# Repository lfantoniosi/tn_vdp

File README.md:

# TN VDP 

# Latest updates:

## 2023-06-20: V3 Main Board with audio fix (Tang20k only)

New V3 board with audio fix has been submitted. Check the kicad folder for gerbers. It requires few new components that you can read on the board. Pretty simple: 10uf capacitor and an optional cinch connector. I will not be updating the BOM lists. WIP project. For a 9958 socket, turn off GromClk (Jumper 3). Leave CpuClk on (Jumper4).

## 2023-06-20: V9958 Socket (V3 Tang20K)

The V9958 drop-in socket (SDIP-64) has been submitted. Check the kicad folder. Code has been improved for Omega MSX compatibility. SDIP pin header are hard to find. Check AliExpress for **"1.778mm Pitch Single Row Male Round Pin Header"**. Not including links they aren't persistent. You need a V3 main board as well for the Tang20K. 

**Note** My Omega MSX has the RAM expansion module and I found out it has incompatiblity with the Tang (seems to be too noisy). If you get issues with IDE controllers, try removing some RAM chips from higher banks. I left my Omega with only 2MB. It's not a PSU problem but rather a routing issue that plagues the Omega for some time.

# Project details
 
## Tang Nano 9K TMS9118A VDP

This project recreates the TMS9118A (and its TMS9928A/TMS9929A
variants) in FPGA using the over the counter Sipeed's Tang Nano 9K
board plus a designed set of boards to be stacked on top where the
TMS9118 was located.

TN VDP v1 uses
[Matthew Haggerty's F18A core](https://github.com/dnotq/f18a), which
is completely compatible with the original Texas Instruments VDP, but
adds
[additional video modes, sprites and color capabilities](https://dnotq.io/f18a/intro.html).

The bitstream file is [here](fpga/tn_vdp_v1/impl/pnr/tn_vdp.fs)

## Version 2.0

The new version supports audio over HDMI. There is no more VGA output. You'll need to pull the pre-amplified audio from somewhere in the computer and connect the **AUDIO** pin on the tn-vdp socket. **MODE1** is not used for TMS9918 cores.

This requires the v2 board sets as well the v2 bitstream (socket board + mainboard). See below gerber files.

There are 2 bitstreams for v2:

[TMS9918](fpga/tn_vdp_v2_v9918/impl/pnr/tn_vdp.fs)

## V9958 32KB VRAM

There is a new core for the v2 boards implemented from ESE-MSX3. The bitstream can be used on the same v2 board sets for the TMS9918:

[V9958](fpga/tn_vdp_v2_v9958/impl/pnr/tn_vdp_v9958.fs)

But for the V9958 you need to pull the A1 address line from somewhere in the computer and connect to pin **MODE1** on the socket to use the full capabilites of the V9958.

## V9958 128KB VRAM: Tang Nano 20K

The v3 of the fpga code and mainboard is for use on a Tang Nano 20K only. There are no other versions for Tang Nano 20K other than V9958 128K. If you need a 9918 use the Tang Nano 9K instead. The socket for the TMS9118 is the same from v2. A socket for a V9958 replacement is in the works.

See instructions below for programming it.

**Note** The gromclk signal has been retired from V9958 128K (no MSX ever uses it). So instead turning this jumper on puts the VDP in no-wait mode, full speed 27Mhz. Turning off it makes the VDP at normal speed (for VDP commands).

## NABU PC Floppy images

Bootable 80 colums for NABU PC CP/M 3 images can be downloaded here (flux and HxC2001): 

[NABU PC images](https://drive.google.com/file/d/1nU48-01ozhA_n-ZHN1SCNINqFqhcBxUN/view?usp=sharing)

## Gerber files

The gerber files can be located inside each KiCad project:

### V1 Boards
[MainBoard for NABU](kicad/tn_vdp_v1_slim/gerber.zip)

[MainBoard for TI-99/4A (FAT)](kicad/tn_vdp_v1_fat/gerber.zip)

[VGA breakout](kicad/tn_vdp_v1_vga/gerber)

[Compact board using SMD components](kicad/tn9k_f18a_compact/gerber.zip)
See the [separate README](kicad/tn9k_f18a_compact/README.md) for BOM ipand additional information.

The VGA module is optional, only if you want VGA output.

### V2 Boards

[MainBoard v2](kicad/tn_vdp_v2_board/gerber.zip)

[Socket v2](kicad/tn_vdp_v2_socket/gerber.zip)

### V3 Boards: Tang Nano 20K ONLY!

[MainBoard v3](kicad/tn_vdp_v3_board/gerber.zip)

[Socket v2](kicad/tn_vdp_v2_socket/gerber.zip) (same TMS9918 socket as v2)

## Gowin IDE
Follow this link to install the Gowin's IDE:

**Note: The code can be built and programmed using the latest Education Version 1.9.8.11 - The Education EDA does not require a license. DO NOT USE THE BETA EDA/PROGRAMMER.**

[IDE Installation](https://wiki.sipeed.com/hardware/en/tang/Tang-Nano-Doc/install-the-ide.html)

The FPGA series is GW1NR and the Device is GW1NR-9C. Use Embedded Flash Mode for permanent programming. Make sure the bitstream is set to Load Rate of 25Mhz (or higher) in the Project -> Configuration -> BitStream: Loading Rate (MHZ). The maximum for this device is 25 Mhz.

## Programming the FPGA

**Gowin Programmer**
Together Gowin IDE you find the programmer or you can install the programmer stand alone. Check the Gowin IDE instructions

**openFPGALoader**
Alternatively you can use the openFPGALoader but it requires changing the FTDI drivers through zadig. Follow the official page for instructions

The [openFPGALoader](https://github.com/trabucayre/openFPGALoader)
tool can be used to program the FPGA from the command line.

```
sudo openFPGALoader -b tangnano9k tn_vdp.fs
```

## Standalone test

The board has a standalone boot screen when you connect it to the USB-C and HDMI only. This will tell the FPGA has been programmed with success.

The v3 Tang Nano 20K has no standalone boot screen.

## Building:

The Tang Nano 9K board can be purchased on AliExpress or ebay.

The boards gerber files are inside each kicad project gerber folders.

## V1 BOM

The BOM for the NABU and FAT v1 variants can be found here [DigiKey BOM](https://www.digikey.ca/short/2t98zrjw)

Or transcribed here
```
Qty | Part Number                | Description
----+----------------------------+----------------------------------
1x  | 123-A-HDF15A-KG-TAXB-ND    | CONN D-SUB HD RCPT 15P R/A SLDR
3x  | 123-AR20-HZL-TT-ND         | CONN IC DIP SOCKET 20POS TIN
2x  | S7022-ND                   | CONN HDR 24POS 0.1 TIN PCB
1x  | 449-KT04RTH-ND             | SWITCH SLIDE DIP 4POS 25MA 24V
3x  | 296-8503-5-ND              | IC TXRX NON-INVERT 3.6V 20DIP
3x  | 1109PHCT-ND CAP            | CER 0.1UF 50V X7R AXIAL
2x  | 2057-PH2RA-16-UA-ND        | CONN HEADER R/A 16POS 2.54MM
2x  | A835AR-ND                  | CONN HDR DIP POST 20POS GOLD
1x  | ED3048-5-ND                | CONN IC DIP SOCKET 40POS TIN
1x  | 2057-ICM-640-1-GT-HT-ND    | MACHINE PIN SOCKET, IC, DIP, 40P
1x  | 1528-5294-ND               | GPIO RIBBON CABLE 2X10 IDC CABLE
3x  | CF14JT2K20CT-ND            | RES 2.2K OHM 5% 1/4W AXIAL
2x  | CF14JT47R0CT-ND            | RES 47 OHM 5% 1/4W AXIAL
3x  | CF14JT4K70CT-ND            | RES 4.7K OHM 5% 1/4W AXIAL
3x  | CF14JT1K00CT-ND            | RES 1K OHM 5% 1/4W AXIAL
3x  | F14JT470RCT-ND             | RES 470 OHM 5% 1/4W AXIAL
1x  | 497-4547-1-ND              | DIODE SCHOTTKY 20V 1A DO41
```
**Notes:**

1) CONN HDR DIP POST 20POS GOLD: It is expensive on DigiKey but it can be sourced elsewhere cheaper, even Amazon.
2) GPIO RIBBON CABLE 2X10 IDC CABLE : It was supposed to be 2x8 but is out of stock. The 2x10 just works. Or build your own.
3) The capacitors need to be soldered manually on the bottom of each IC's. There are no pads for them to reduce the size of the board. See back.jpg photo for reference under images folder.
4) There are 2 DIP 40 sockets in this list: one machined other normal. The machined socket you will use to connect the board on top, thus protecting the pins. The machined pins for the board will connect easily to a machined socket. Then you stack this machined socked over the normal one (notice little force is necessary), and then finally you stack them at the NABU PC's TMS9118 socket. This will protect both the NABU and the tn_vdp pins.

# V2 BOM
```
Qty | Part Number                | Description
----+----------------------------+----------------------------------
3x  | 123-AR20-HZL-TT-ND         | CONN IC DIP SOCKET 20POS TIN
1x  | 2057-ICM-308-1-GT-HT-ND    | MACHINE PIN SOCKET, IC, DIP, 8P
3x  | 296-8503-5-ND              | IC TXRX NON-INVERT 3.6V 20DIP
4x  | BC1084CT-ND                | CAP CER 0.1UF 50V X7R RADIAL
1x  | 1528-5294-ND               | GPIO RIBBON CABLE 2X10 IDC CABLE
1x  | 497-4547-1-ND              | DIODE SCHOTTKY 20V 1A DO41
1x  | MCP3202-CI/P-ND            | IC ADC 12BIT SAR 8DIP
2x  | S7022-ND                   | CONN HDR 24POS 0.1 TIN PCB
2x  | A835AR-ND                  | CONN HDR DIP POST 20POS GOLD
4x  | 732-5301-ND                | CONN HEADER VERT 20POS 2.54MM 
1x  | 10129379-920001BLF-ND      | CONN HEADER R/A 20POS 2.54MM
4x  | S9000-ND                   | CONN JUMPER SHORTING TIN
```
**Notes:**

I find these header pins 2.54mm too expensive on DigiKey. I'd advise you to procure them on AliExpress, longer wait time but way cheaper. 

# V3 BOM

The V3 BOM is almost identically to V2 except that I added a trimmer for the audio and I returned with the DIP switch 4 pos:

```
Qty | Part Number                | Description
----+----------------------------+----------------------------------
1x  | 3339P-1-103LF              | TRIMMER 10K OHM 0.5W PC PIN TOP
1x  | 449-KT04RTH-ND             | SWITCH SLIDE DIP 4POS 25MA 24V
```

## Jumper Settings

These are the jumper. Closed means ON:
```
USR1 : SPR MAX - Turn it on for 32 sprites per line (9958 this puts 8 sprites for mode 0)
USR2 : SCANLIN - Turn it on for scanlines
USR3 : GROMCLK - Turn it on to have GROM CLOCK enabled, Disabling it puts CPUCLK on pin 37 (9128/29)
USR4 : CPUCLK  - Turn if on to have CPU CLOCK on pin 38 (9929/29 and 9128/29)
```

## Assembling Instructions

You shouldn't have problem assembling it as all components are labeled. Just remember the 2 pin strips for the TMS9118 slot goes under the board as well the 3 caps. Everything else it on the top side. I personally prefer soldering the female header on the FPGA board. Mind the orientation of the **DIP switch** as the image below.
```
1) solder the 3 DIP-20 sockets on top side
2) for each socket, solder one axial caps under the board connecting pins GND and VCC the back image below
3) solder the mini-switch on top side, mind hte numbering according to the text
4) solder the two male machine strips under the board (20 pins each strip)
5) solder the male pins that came with the Tang Nano 9K board on the top side of the board (24 pins each)
6) solder the 8x2 right angle header (optional for VGA)
6) solder the 2 female headers under the Tang Nano 9K board
7) install the 3 74VLC256 chips. Mind the half-moon orientation
7) plug the Tang Nano 9K on the male pins, mind the HDMI and UBS-C orientation as printed on the board
8) configure the dip-switches
```

## DIP switches
```
USR1 - 32 sprite per line (TMS9918), 8 sprites per line (V9958)
USR2 - scanlines
USR3 - pin 37: gromclk (on), cpuclk (off)
USR4 - pin 38: cpuclk (on), NC (off)

TMS9918A: (NABU-PC, CX5M)
USR3 - on
USR4 - on

TMS9928/29A
USR3 - on
USR4 - off

TMS9918
USR3 - on
USR4 - on

TMS9128/29
USR3 - off
USR4 - off
```

## V3 Programming

The Tang Nano 20K version is a bit more convoluted to install. We need to reconfigure the PLL nets.

First using the programmer flash this LITEX on the board:

[Tang Nano 20K LITEX](fpga/tn_vdp_v3_v9958/res/pnr/tang_nano_20k_litex.fs)

Disconnect and re-connect to your PC.

Go to device manager and change the properties for the USB Serial Port (COMxx) for your Tang Nano 20K (disconnect/reconnect the board and see wich one disappear to identify it). Change the Port Settings: Bits per second to 115200 and Apply.

Now you need a terminal application like Tera Term to connect to serial port.

Pressione Control-X Control-C and ENTER

You should see the LITE terminal, type:

```
pll_clk O0=50M
pll_clk O1=125M
pll_clk -s
```

After that you can just flash the v3 core from here:

[V9958 128K](fpga/tn_vdp_v3_v9918/impl/pnr/tn_vdp_v3_v9958.fs)

Now the board is ready to use.

## Images

You need to solder the capacitors under each IC's. I made this way to reduce the size of the board.

And the final board stacked up. To avoid plugging the board inverted there are two labels on it: **USB-C SIDE** and **HDMI SIDE**. The orientation of the board towards the TMS9118 slot is the USB-C up (pin 1 of TMS9118). The TMS9118 pin number 1 and 40 are printed under it.

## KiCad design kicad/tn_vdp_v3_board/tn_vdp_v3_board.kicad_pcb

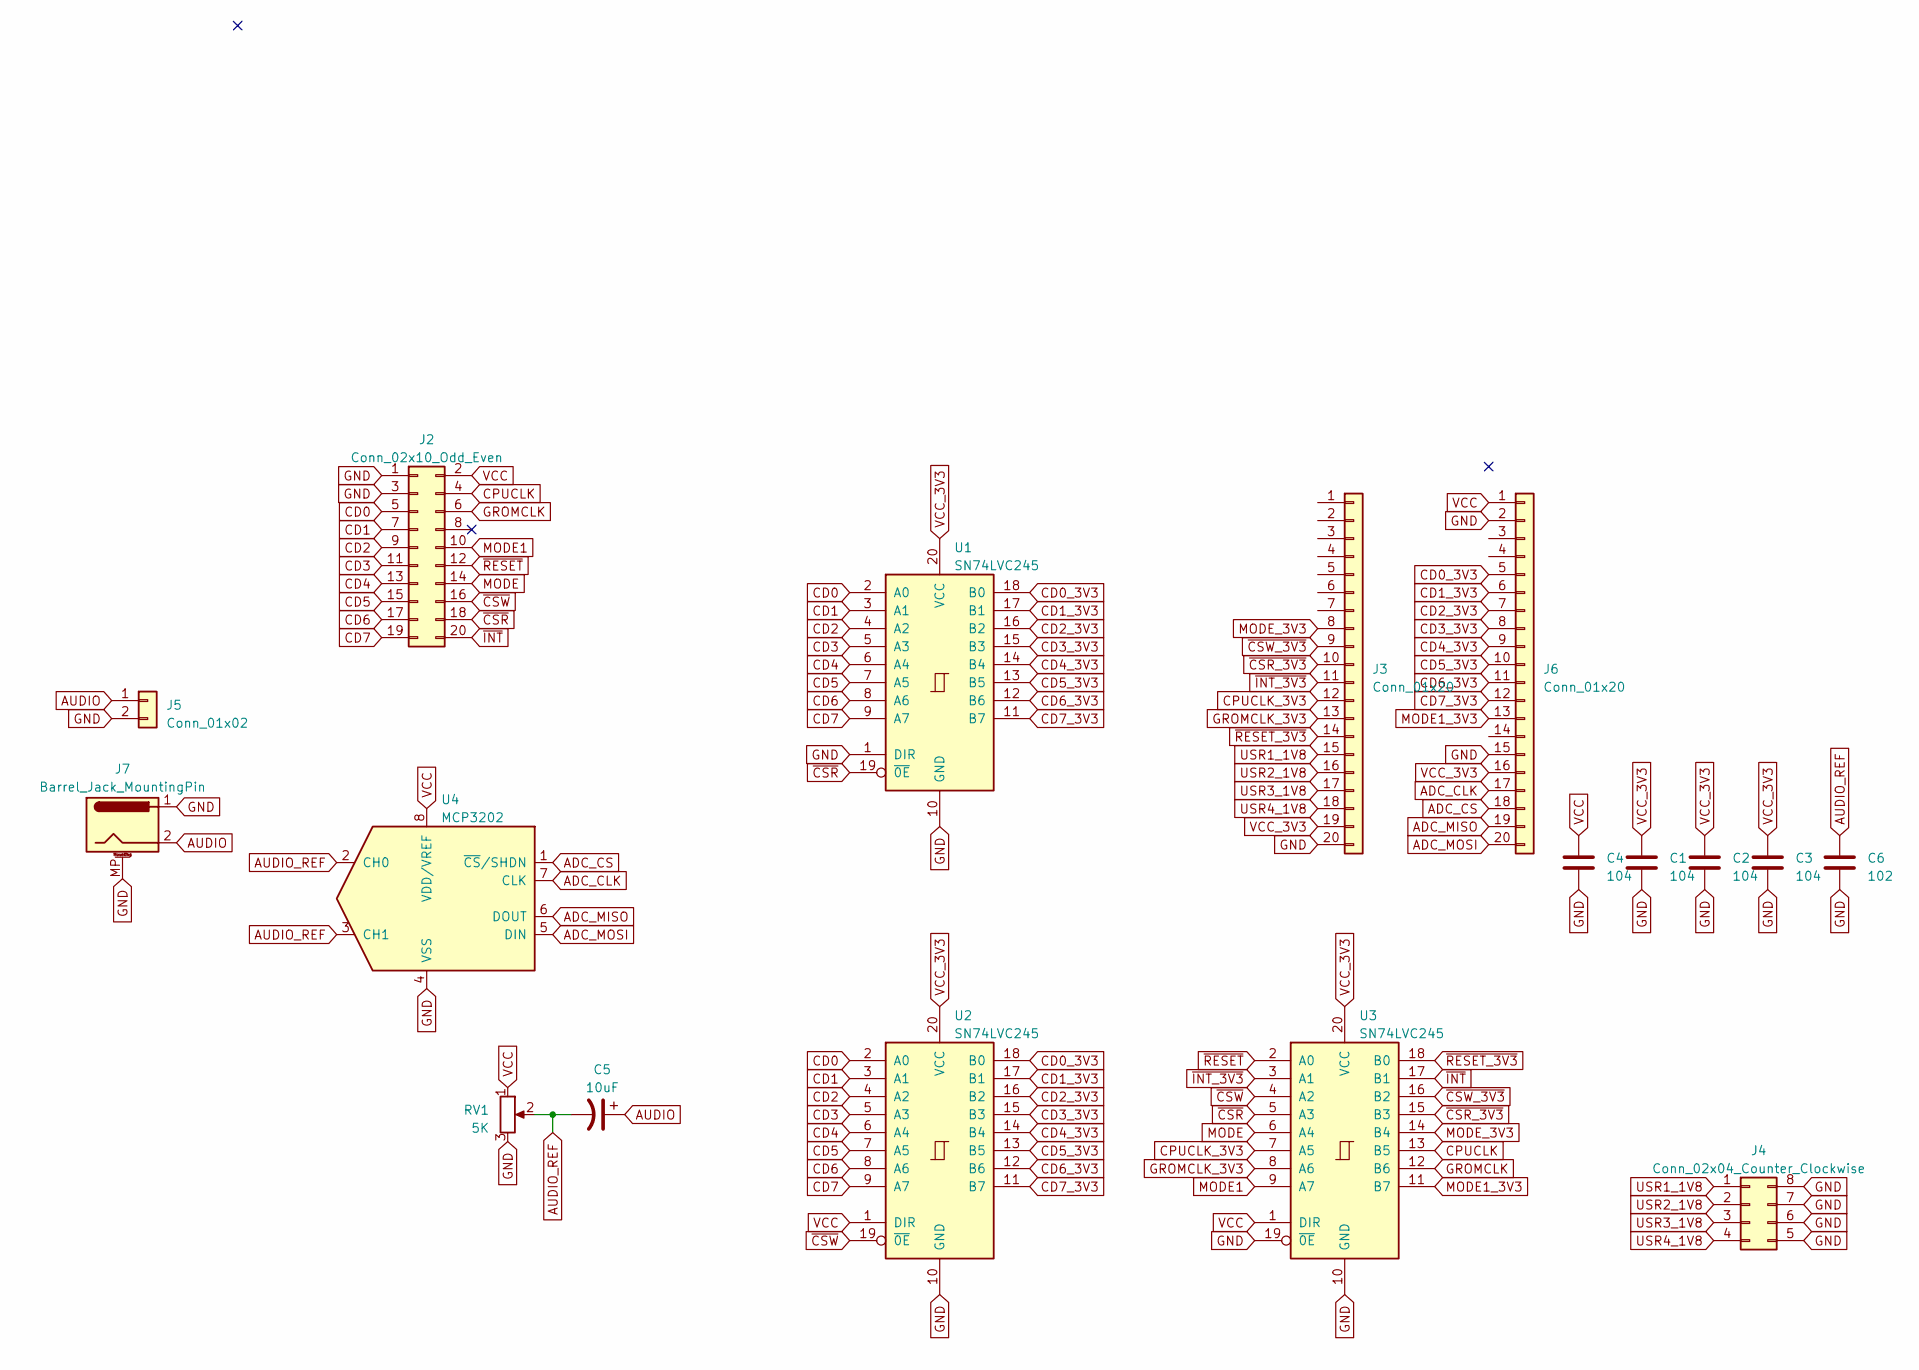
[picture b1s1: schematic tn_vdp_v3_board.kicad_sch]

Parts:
C1, C2, C3, C4: 104; C_Disc_D5.0mm_W2.5mm_P2.50mm
C5: 10uF; CP_Radial_D5.0mm_P2.50mm
C6: 102; C_Disc_D5.0mm_W2.5mm_P2.50mm
J2: Conn_02x10_Odd_Even; PinHeader_2x10_P2.54mm_Vertical
J3, J6: Conn_01x20; PinHeader_1x20_P2.54mm_Vertical
J4: Conn_02x04_Counter_Clockwise; SW_DIP_SPSTx04_Slide_6.7x11.72mm_W7.62mm_P2.54mm_LowProfile
J5: Conn_01x02; PinHeader_1x02_P2.54mm_Horizontal
J7: Barrel_Jack_MountingPin; BarrelJack_CUI_PJ-063AH_Horizontal_CircularHoles
RV1: 5K; Potentiometer_Piher_PT-6-V_Vertical
U1, U2, U3: SN74LVC245; DIP-20_W7.62mm_Socket_LongPads
U4: MCP3202; DIP-8_W7.62mm_LongPads

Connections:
ADC_CLK: J6.17, U4.7 (CLK)
ADC_CS: J6.18, U4.1 (~CS/SHDN)
ADC_MISO: J6.19, U4.6 (DOUT)
ADC_MOSI: J6.20, U4.5 (DIN)
AUDIO: C5.1, J5.1, J7.2
AUDIO_REF: C5.2, C6.1, RV1.2, U4.2 (CH0), U4.3 (CH1)
CD0: J2.5, U1.2 (A0), U2.2 (A0)
CD0_3V3: J6.5, U1.18 (B0), U2.18 (B0)
CD1: J2.7, U1.3 (A1), U2.3 (A1)
CD1_3V3: J6.6, U1.17 (B1), U2.17 (B1)
CD2: J2.9, U1.4 (A2), U2.4 (A2)
CD2_3V3: J6.7, U1.16 (B2), U2.16 (B2)
CD3: J2.11, U1.5 (A3), U2.5 (A3)
CD3_3V3: J6.8, U1.15 (B3), U2.15 (B3)
CD4: J2.13, U1.6 (A4), U2.6 (A4)
CD4_3V3: J6.9, U1.14 (B4), U2.14 (B4)
CD5: J2.15, U1.7 (A5), U2.7 (A5)
CD5_3V3: J6.10, U1.13 (B5), U2.13 (B5)
CD6: J2.17, U1.8 (A6), U2.8 (A6)
CD6_3V3: J6.11, U1.12 (B6), U2.12 (B6)
CD7: J2.19, U1.9 (A7), U2.9 (A7)
CD7_3V3: J6.12, U1.11 (B7), U2.11 (B7)
CPUCLK: J2.4, U3.13 (B5)
CPUCLK_3V3: J3.12, U3.7 (A5)
GND: C1.2, C2.2, C3.2, C4.2, C6.2, J2.1, J2.3, J3.20, J4.5, J4.6, J4.7, J4.8, J5.2, J6.2, J6.15, J7.1, J7.MP (MountPin), RV1.3, U1.1 (DIR), U1.10 (GND), U2.10 (GND), U3.10 (GND), U3.19 (~0E), U4.4 (VSS)
GROMCLK: J2.6, U3.12 (B6)
GROMCLK_3V3: J3.13, U3.8 (A6)
MODE: J2.14, U3.6 (A4)
MODE1: J2.10, U3.9 (A7)
MODE1_3V3: J6.13, U3.11 (B7)
MODE_3V3: J3.8, U3.14 (B4)
USR1_1V8: J3.15, J4.1
USR2_1V8: J3.16, J4.2
USR3_1V8: J3.17, J4.3
USR4_1V8: J3.18, J4.4
VCC: C4.1, J2.2, J6.1, RV1.1, U2.1 (DIR), U3.1 (DIR), U4.8 (VDD/VREF)
VCC_3V3: C1.1, C2.1, C3.1, J3.19, J6.16, U1.20 (VCC), U2.20 (VCC), U3.20 (VCC)
~CSR_3V3: J3.10, U3.15 (B3)
~CSR: J2.18, U1.19 (~0E), U3.5 (A3)
~CSW_3V3: J3.9, U3.16 (B2)
~CSW: J2.16, U2.19 (~0E), U3.4 (A2)
~INT_3V3: J3.11, U3.3 (A1)
~INT: J2.20, U3.17 (B1)
~RESET_3V3: J3.14, U3.18 (B0)
~RESET: J2.12, U3.2 (A0)

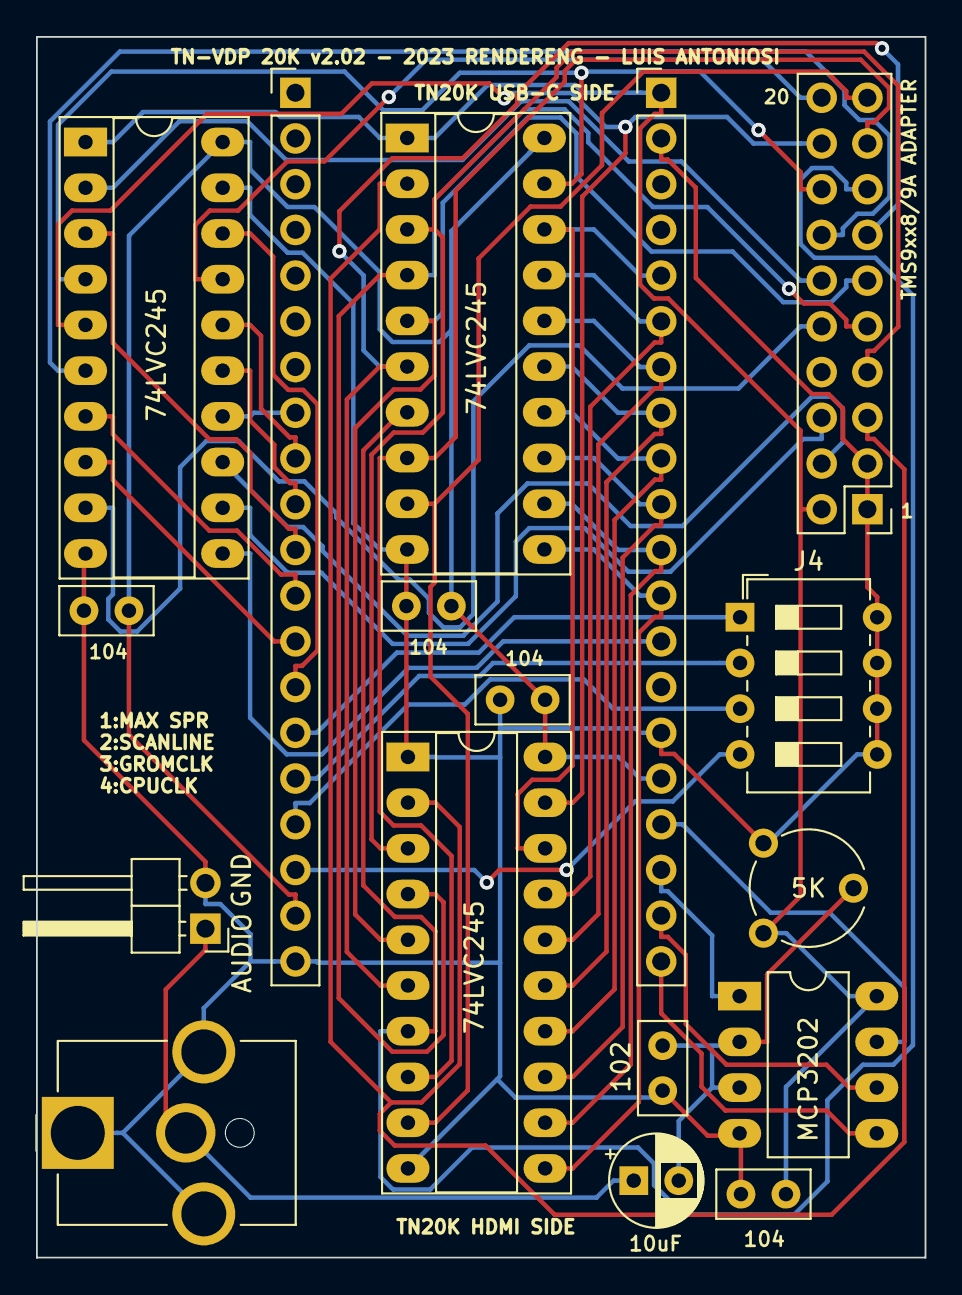
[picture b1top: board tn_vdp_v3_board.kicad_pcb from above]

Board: 2 copper layers, 49.4 x 67.8 mm, 17 parts (0 on the bottom side), 45 nets.

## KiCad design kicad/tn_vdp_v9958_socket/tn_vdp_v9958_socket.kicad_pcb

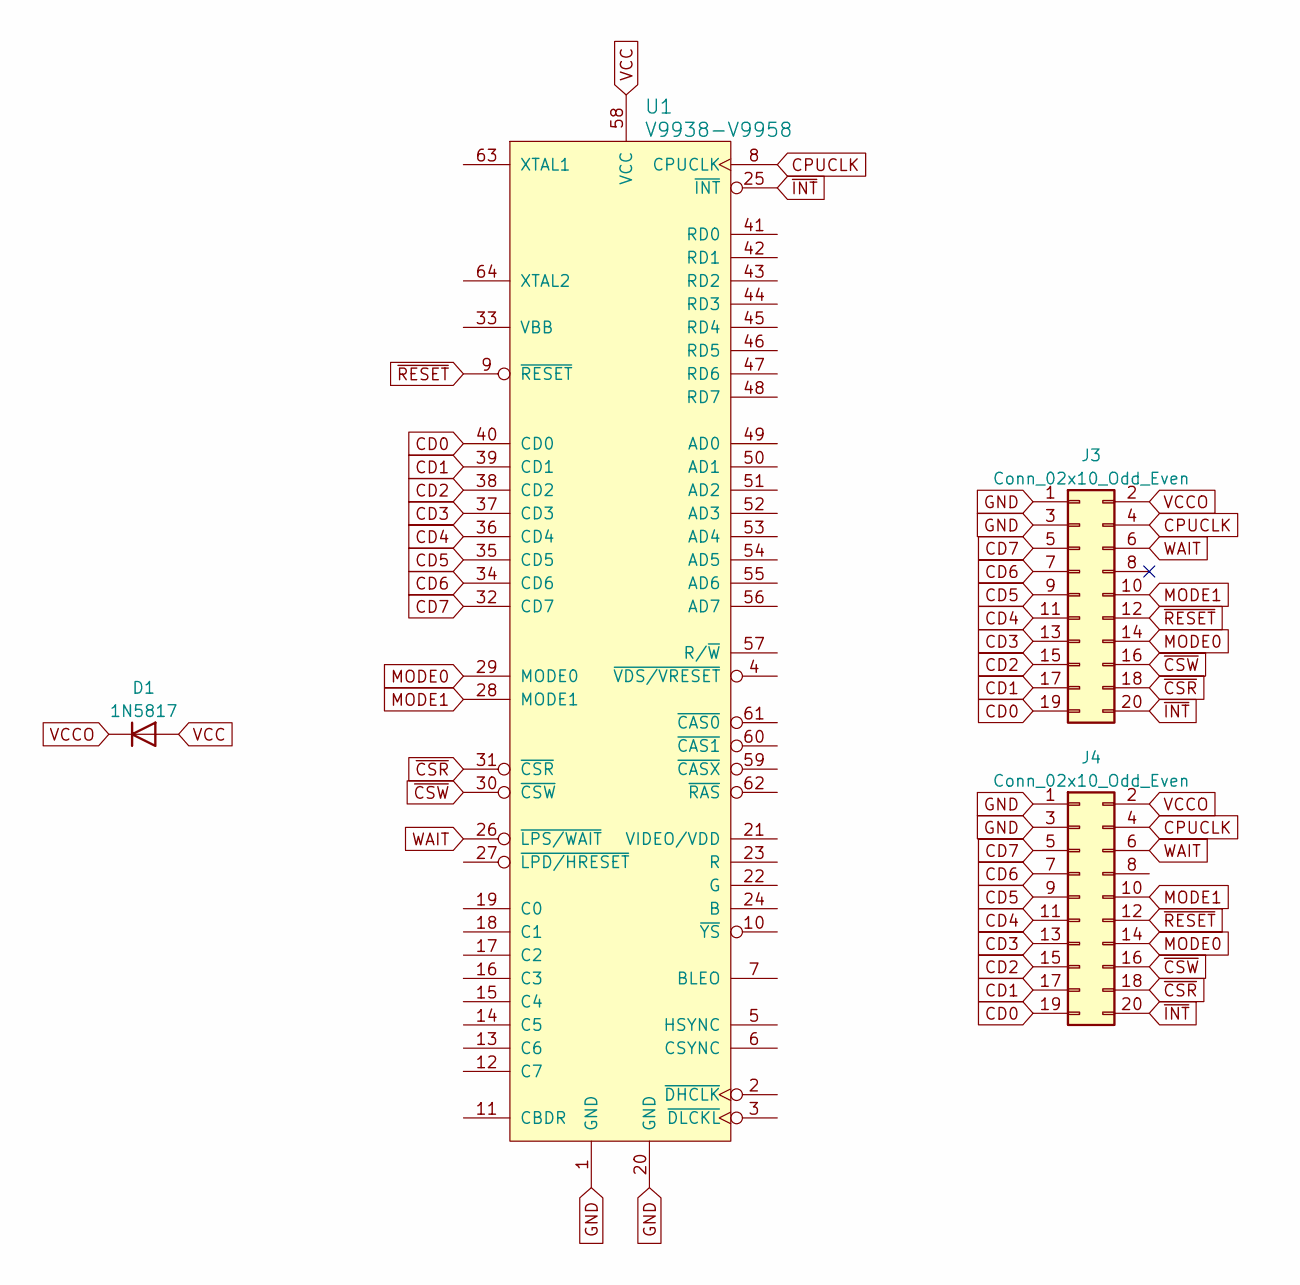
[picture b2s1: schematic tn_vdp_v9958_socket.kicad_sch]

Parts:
D1: 1N5817; D_DO-41_SOD81_P10.16mm_Horizontal
J3, J4: Conn_02x10_Odd_Even; PinHeader_2x10_P2.54mm_Vertical
U1: V9938-V9958; IC_SDIP64_600

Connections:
CD0: J3.19, J4.19, U1.40 (CD0)
CD1: J3.17, J4.17, U1.39 (CD1)
CD2: J3.15, J4.15, U1.38 (CD2)
CD3: J3.13, J4.13, U1.37 (CD3)
CD4: J3.11, J4.11, U1.36 (CD4)
CD5: J3.9, J4.9, U1.35 (CD5)
CD6: J3.7, J4.7, U1.34 (CD6)
CD7: J3.5, J4.5, U1.32 (CD7)
CPUCLK: J3.4, J4.4, U1.8 (CPUCLK)
GND: J3.1, J3.3, J4.1, J4.3, U1.1 (GND), U1.20 (GND)
MODE0: J3.14, J4.14, U1.29 (MODE0)
MODE1: J3.10, J4.10, U1.28 (MODE1)
VCC: D1.2 (A), U1.58 (VCC)
VCCO: D1.1 (K), J3.2, J4.2
WAIT: J3.6, J4.6, U1.26 (~LPS/WAIT)
~CSR: J3.18, J4.18, U1.31 (~CSR)
~CSW: J3.16, J4.16, U1.30 (~CSW)
~INT: J3.20, J4.20, U1.25 (~INT)
~RESET: J3.12, J4.12, U1.9 (~RESET)

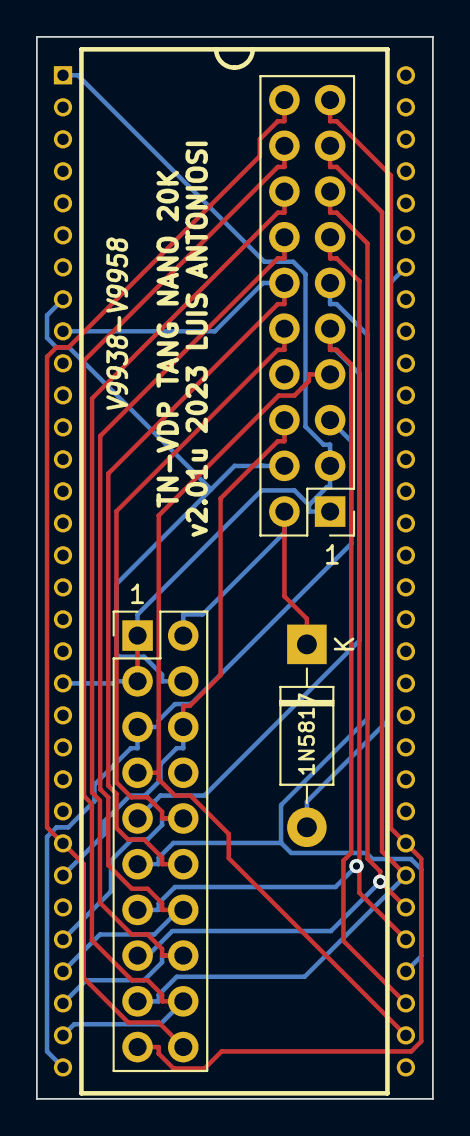
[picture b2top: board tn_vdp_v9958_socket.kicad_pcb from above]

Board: 2 copper layers, 22.0 x 59.0 mm, 4 parts (0 on the bottom side), 19 nets.

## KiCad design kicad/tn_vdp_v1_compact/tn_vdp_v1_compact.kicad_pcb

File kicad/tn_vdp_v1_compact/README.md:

# TMS9918A compatible VDP based on Tang Nano 9k - Compact (SMD) version

This version is a compact variant of the tn_vdp_v1 board that directly
fits into the VDP socket of the TI-99/4A.  It uses SMD components and
has the same size as the Tang Nano 9k board.  It comes with a VGA
breakout connector that can be directly used if the space in the host
machine allows it, or be snapped off, mounted on a breakout panel on
the back of the host machine and be connected with a ribbon cable.

## BOM

|Item|Qty|Reference(s)|Value       |Description                              |Part Number            |Footprint|URL                                                               |
|----|---|------------|------------|-----------------------------------------|-----------------------|---------|------------------------------------------------------------------|
|1   |1  |            |Tang Nano 9k|FPGA development board                   |                       |         |https://wiki.sipeed.com/hardware/en/tang/Tang-Nano-9K/Nano-9K.html|
|2   |1  |U1          |1G08        |Single AND gate                          |SN74LVC1G08            |SOT-23-5 |http://www.ti.com/lit/sg/scyt129e/scyt129e.pdf                    |
|3   |1  |U4          |74LCX16245  |16 bit buffer                            |74LCX16245MTD          |TSSOP-48 |https://www.onsemi.com/pdf/datasheet/mc74lcx16245-d.pdf           |
|4   |1  |D1          |D_Schottky  |Schottky diode                           |MBR0530                |SOD-123  |                                                                  |
|5   |3  |R1, R5, R9  |4.7K        |Resistor SMD 0603                        |                       |0603     |                                                                  |
|6   |3  |R2, R6, R10 |2.2K        |Resistor SMD 0603                        |                       |0603     |                                                                  |
|7   |3  |R3, R7, R11 |1K          |Resistor SMD 0603                        |                       |0603     |                                                                  |
|8   |3  |R4, R8, R12 |470         |Resistor SMD 0603                        |                       |0603     |                                                                  |
|9   |2  |R13, R14    |47          |Resistor SMD 0603                        |                       |0603     |                                                                  |
|10  |1  |C1          |100nF       |Capacitor SMD 0603                       |                       |0603     |                                                                  |
|11  |21 |J1          |            |PCB pin Mill-Max                         |3157-0-00-15-00-00-03-0|         |                                                                  |
|12  |1  |J6          |VGA         |Pin Header 2.54mm Horizontal 16pos       |68021-116HLF           |         |                                                                  |
|13  |1  |J2          |VGA         |Ribbon cable 16 pin 2x8 solder to 2x8 IDC|                       |         |https://de.aliexpress.com/item/1005004165880347.html              |
|14  |1  |J5          |VGA         |DB15HD connector, female                 |                       |         |                                                                  |

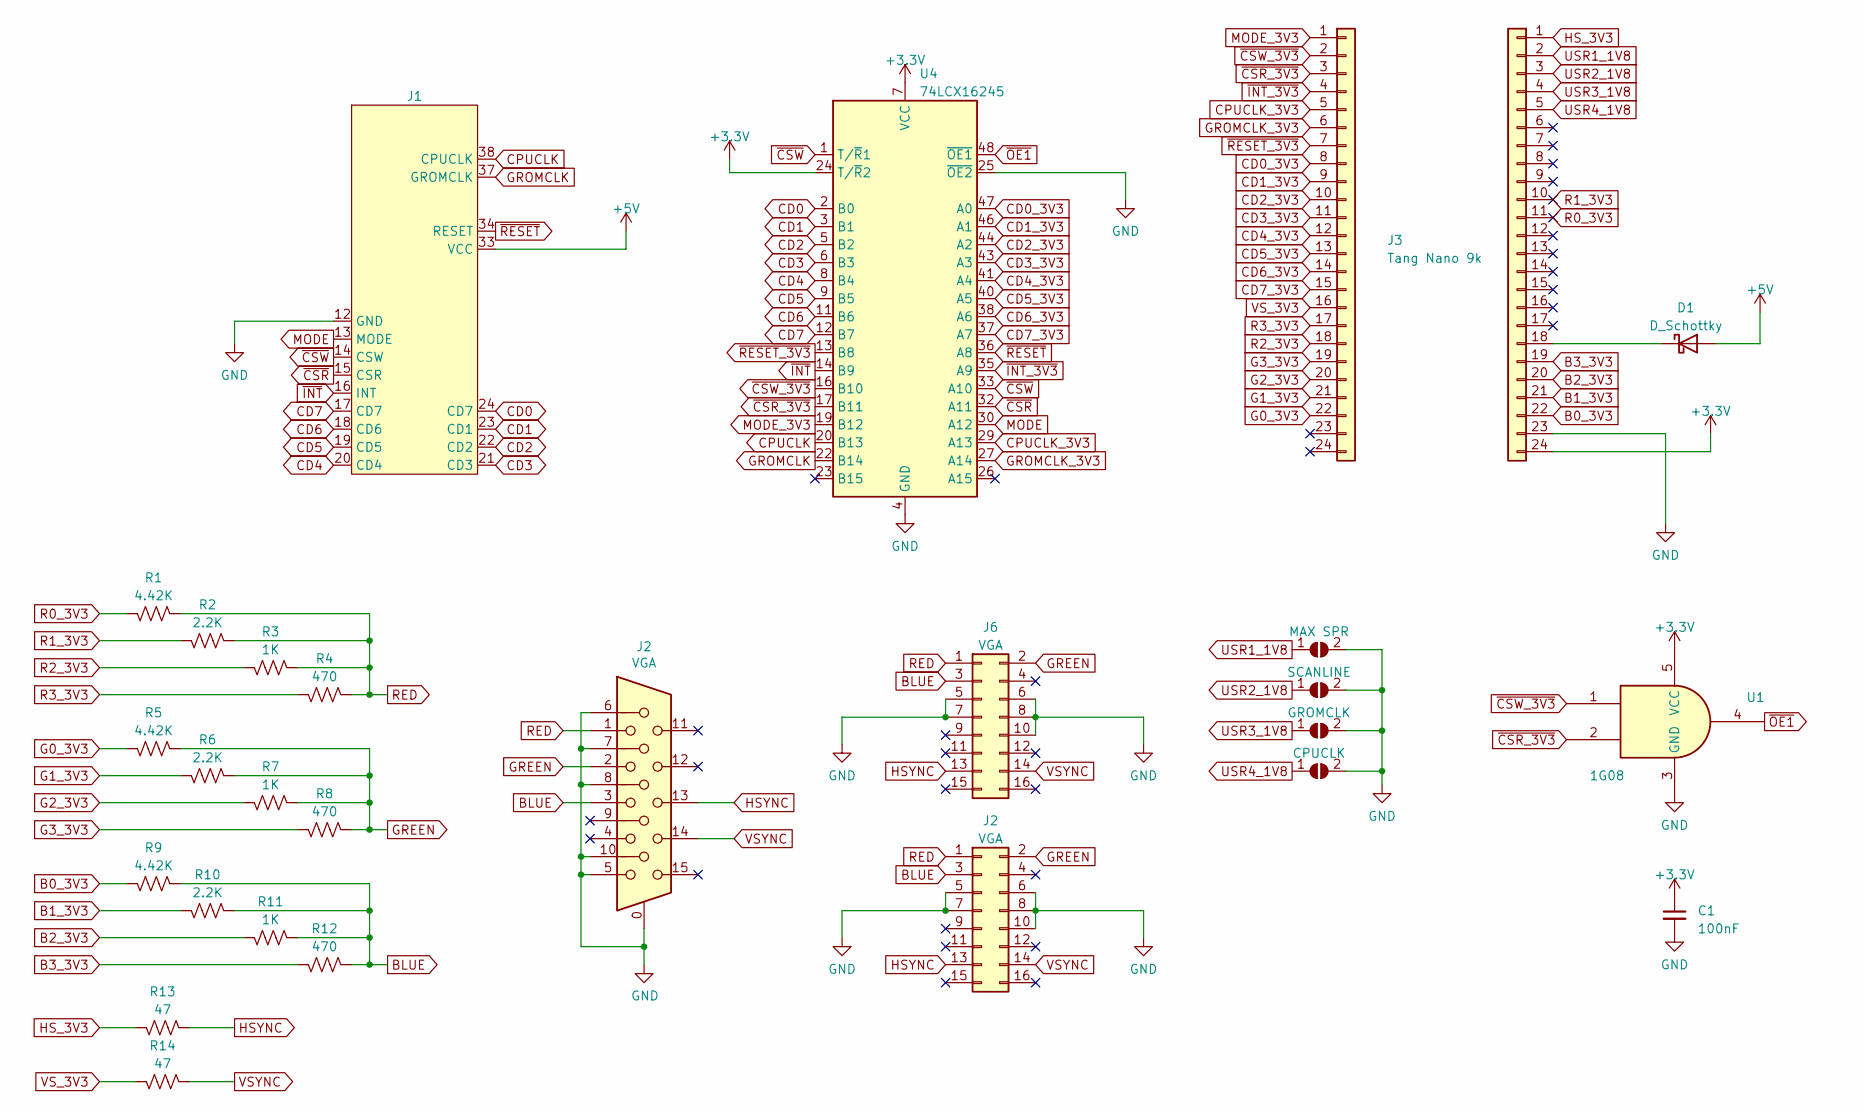
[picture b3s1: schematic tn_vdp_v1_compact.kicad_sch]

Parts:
C1: 100nF; C_0603_1608Metric_Pad1.08x0.95mm_HandSolder; LCSC C2857981
D1: D_Schottky; D_SOD-123; LCSC C2900723
J1: TMS99xxA_Replacement
J2: VGA; DSUB-15-HD_Female_Horizontal_P2.29x1.98mm_EdgePinOffset3.03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
J3: Tang Nano 9k; PinSocket_1x24_P2.54mm_Vertical
J4: TN9k/2; PinSocket_1x24_P2.54mm_Vertical
J6: VGA; PinHeader_2x08_P2.54mm_Vertical
JP1: MAX SPR; SolderJumper-2_P1.3mm_Open_RoundedPad1.0x1.5mm
JP2: SCANLINE; SolderJumper-2_P1.3mm_Open_RoundedPad1.0x1.5mm
JP3: GROMCLK; SolderJumper-2_P1.3mm_Open_RoundedPad1.0x1.5mm
JP4: CPUCLK; SolderJumper-2_P1.3mm_Open_RoundedPad1.0x1.5mm
R1, R5, R9: 4.42K; R_0603_1608Metric_Pad0.98x0.95mm_HandSolder; LCSC C5140130
R2, R6, R10: 2.2K; R_0603_1608Metric_Pad0.98x0.95mm_HandSolder; LCSC C3016472
R3, R7, R11: 1K; R_0603_1608Metric_Pad0.98x0.95mm_HandSolder; LCSC C3016283
R4, R8, R12: 470; R_0603_1608Metric_Pad0.98x0.95mm_HandSolder; LCSC C103660
R13, R14: 47; R_0603_1608Metric_Pad0.98x0.95mm_HandSolder; LCSC C3016437
U1: 1G08; SOT-23-5_HandSoldering; LCSC C7666
U4: 74LCX16245; TSSOP-48_6.1x12.5mm_P0.5mm; LCSC C894789

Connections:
+3.3V: C1.1, J4.24, U1.5 (VCC), U4.7 (VCC), U4.18 (VCC), U4.24 (T/~R2), U4.31 (VCC), U4.42 (VCC)
+5V: D1.2 (A), J1.33 (VCC)
B0_3V3: J4.22, R9.2
B1_3V3: J4.21, R10.2
B2_3V3: J4.20, R11.2
B3_3V3: J4.19, R12.2
BLUE: J2.3, J6.3, R9.1, R10.1, R11.1, R12.1; also elsewhere on the board
CD0: J1.24 (CD7), U4.2 (B0)
CD0_3V3: J3.8, U4.47 (A0)
CD1: J1.23 (CD1), U4.3 (B1)
CD1_3V3: J3.9, U4.46 (A1)
CD2: J1.22 (CD2), U4.5 (B2)
CD2_3V3: J3.10, U4.44 (A2)
CD3: J1.21 (CD3), U4.6 (B3)
CD3_3V3: J3.11, U4.43 (A3)
CD4: J1.20 (CD4), U4.8 (B4)
CD4_3V3: J3.12, U4.41 (A4)
CD5: J1.19 (CD5), U4.9 (B5)
CD5_3V3: J3.13, U4.40 (A5)
CD6: J1.18 (CD6), U4.11 (B6)
CD6_3V3: J3.14, U4.38 (A6)
CD7: J1.17 (CD7), U4.12 (B7)
CD7_3V3: J3.15, U4.37 (A7)
CPUCLK: J1.38 (CPUCLK), U4.20 (B13)
CPUCLK_3V3: J3.5, U4.29 (A13)
G0_3V3: J3.22, R5.2
G1_3V3: J3.21, R6.2
G2_3V3: J3.20, R7.2
G3_3V3: J3.19, R8.2
GND: C1.2, J1.12 (GND), J2.0, J2.5, J2.6, J2.7, J2.8, J2.10, J4.23, J6.5, J6.6, J6.7, J6.8, J6.10, JP1.2 (B), JP2.2 (B), JP3.2 (B), JP4.2 (B), U1.3 (GND), U4.4 (GND), U4.10 (GND), U4.15 (GND), U4.21 (GND), U4.25 (~OE2), U4.28 (GND), U4.34 (GND), U4.39 (GND), U4.45 (GND); also elsewhere on the board
GREEN: J2.2, J6.2, R5.1, R6.1, R7.1, R8.1; also elsewhere on the board
GROMCLK: J1.37 (GROMCLK), U4.22 (B14)
GROMCLK_3V3: J3.6, U4.27 (A14)
HSYNC: J2.13, J6.13, R13.1; also elsewhere on the board
HS_3V3: J4.1, R13.2
MODE: J1.13 (MODE), U4.30 (A12)
MODE_3V3: J3.1, U4.19 (B12)
unnamed: D1.1 (K), J4.18
R0_3V3: J4.11, R1.2
R1_3V3: J4.10, R2.2
R2_3V3: J3.18, R3.2
R3_3V3: J3.17, R4.2
RED: J2.1, J6.1, R1.1, R2.1, R3.1, R4.1; also elsewhere on the board
USR1_1V8: J4.2, JP1.1 (A)
USR2_1V8: J4.3, JP2.1 (A)
USR3_1V8: J4.4, JP3.1 (A)
USR4_1V8: J4.5, JP4.1 (A)
VSYNC: J2.14, J6.14, R14.1; also elsewhere on the board
VS_3V3: J3.16, R14.2
~CSR_3V3: J3.3, U1.2, U4.17 (B11)
~CSR: J1.15 (CSR), U4.32 (A11)
~CSW_3V3: J3.2, U1.1, U4.16 (B10)
~CSW: J1.14 (CSW), U4.1 (T/~R1), U4.33 (A10)
~INT_3V3: J3.4, U4.35 (A9)
~INT: J1.16 (INT), U4.14 (B9)
~OE1: U1.4, U4.48 (~OE1)
~RESET_3V3: J3.7, U4.13 (B8)
~RESET: J1.34 (RESET), U4.36 (A8)

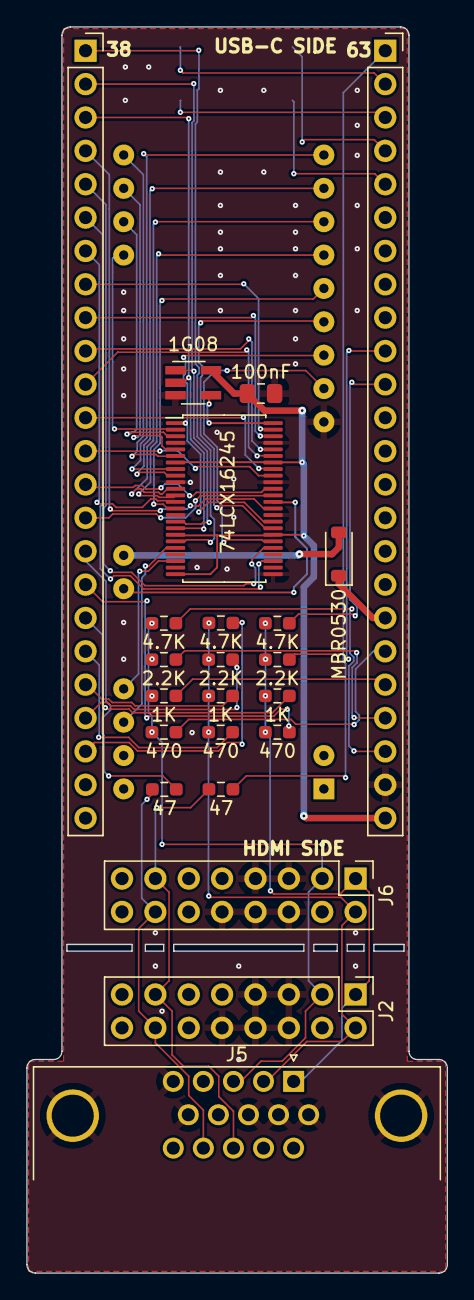
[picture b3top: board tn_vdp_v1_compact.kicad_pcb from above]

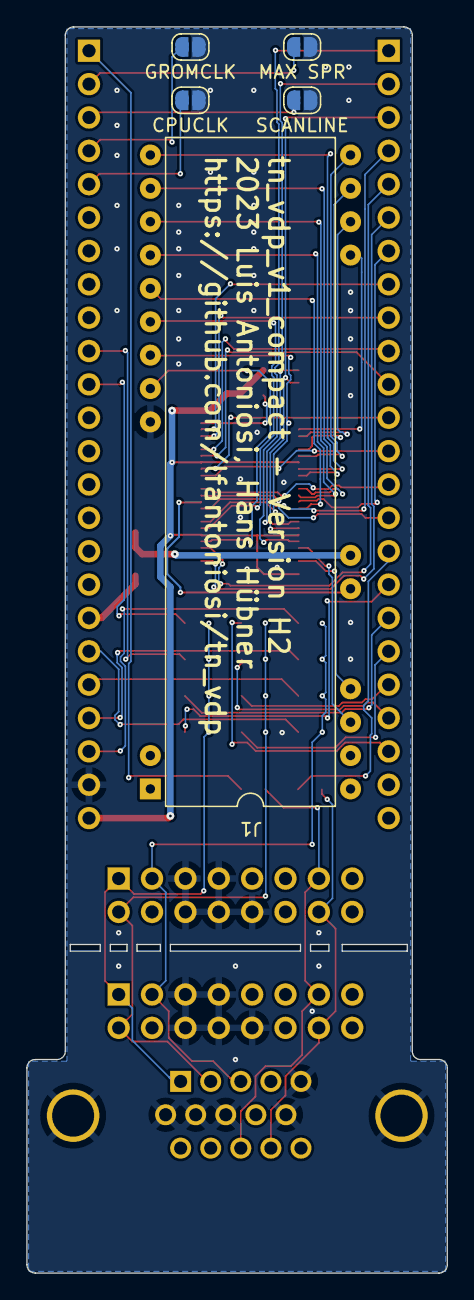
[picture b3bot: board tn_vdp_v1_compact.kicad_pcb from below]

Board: 2 copper layers, 32.0 x 94.9 mm, 28 parts (4 on the bottom side), 58 nets.

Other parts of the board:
J5: VGA; DSUB-15-HD_Female_Horizontal_P2.29x1.98mm_EdgePinOffset3.03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

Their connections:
BLUE: J5.3; also elsewhere on the board
GND: J5.0, J5.5, J5.6, J5.7, J5.8, J5.10; also elsewhere on the board
GREEN: J5.2; also elsewhere on the board
HSYNC: J5.13; also elsewhere on the board
RED: J5.1; also elsewhere on the board
VSYNC: J5.14; also elsewhere on the board

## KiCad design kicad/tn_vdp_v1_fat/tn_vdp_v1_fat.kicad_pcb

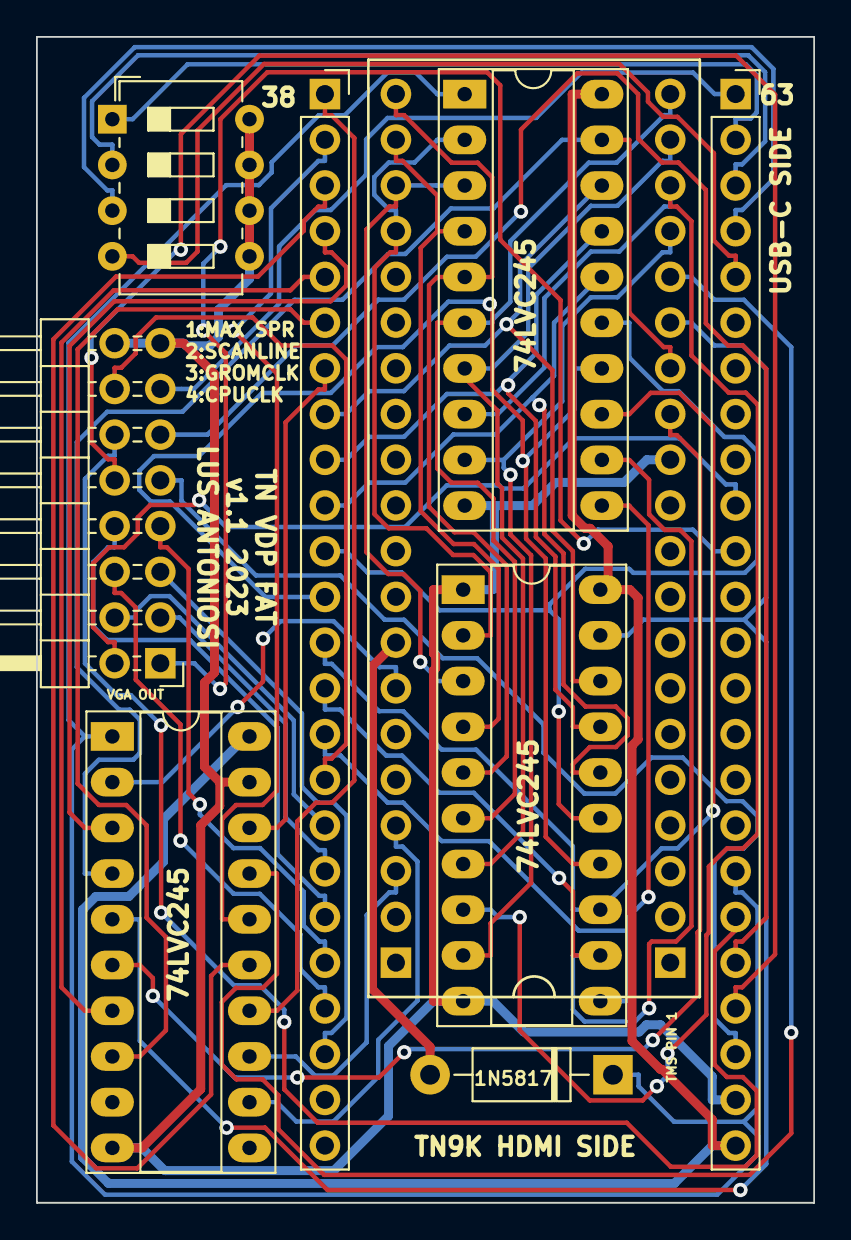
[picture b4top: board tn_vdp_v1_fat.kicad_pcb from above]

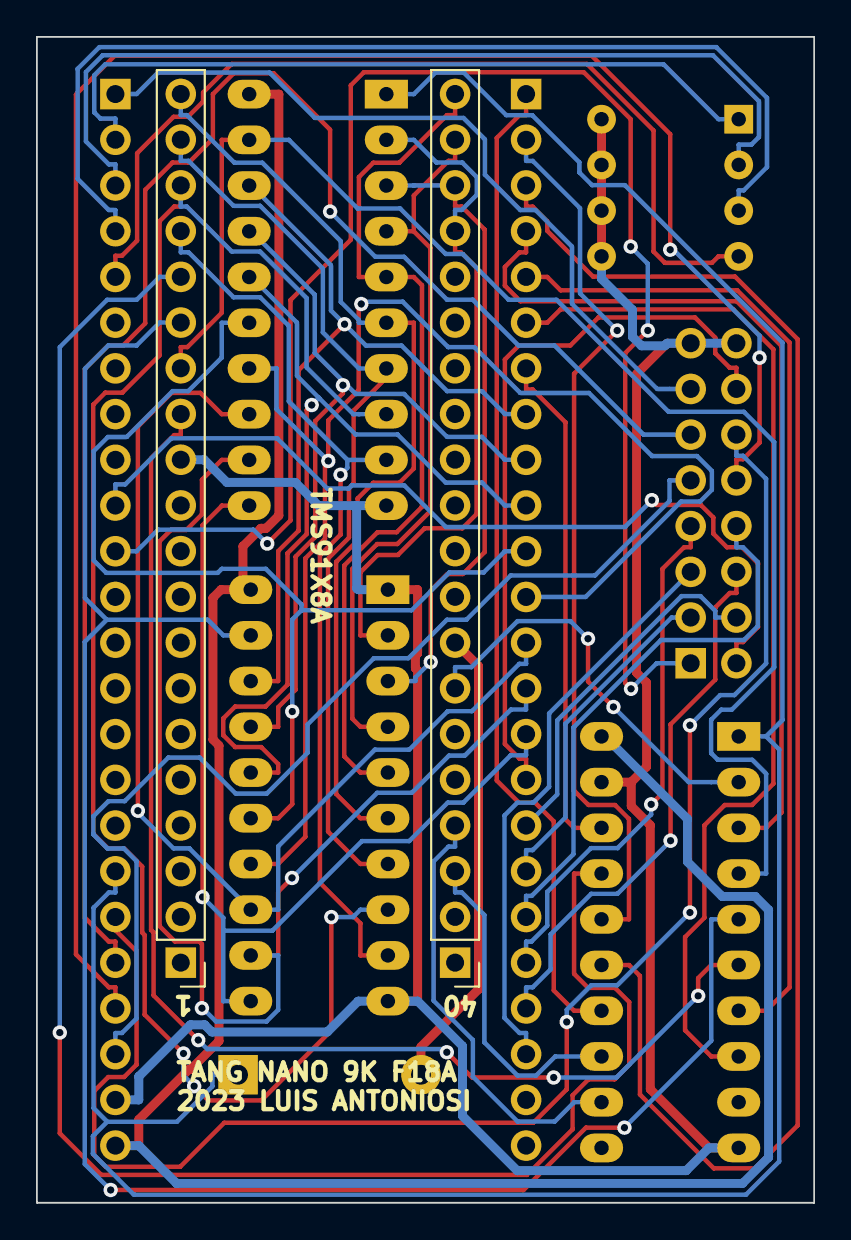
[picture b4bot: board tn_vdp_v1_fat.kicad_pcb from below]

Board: 2 copper layers, 43.2 x 64.8 mm, 10 parts (2 on the bottom side), 52 nets.

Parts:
D1: 1N5817; D_DO-41_SOD81_P10.16mm_Horizontal
J1, J2: Conn_01x20; PinHeader_1x20_P2.54mm_Vertical
J3, J4: Conn_01x24; PinSocket_1x24_P2.54mm_Vertical
J5: Conn_02x04_Counter_Clockwise; SW_DIP_SPSTx04_Slide_6.7x11.72mm_W7.62mm_P2.54mm_LowProfile
J6: Conn_02x08_Odd_Even; PinHeader_2x08_P2.54mm_Horizontal
U1, U2, U3: SN74LVC245; DIP-20_W7.62mm_Socket_LongPads

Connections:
B0_3V3: J4.22, J6.9
B1_3V3: J4.21, J6.10
B2_3V3: J4.20, J6.11
B3_3V3: J4.19, J6.12
CD0: J2.17, U1.2 (A0), U2.2 (A0)
CD0_3V3: J3.8, U1.18 (B0), U2.18 (B0)
CD1: J2.18, U1.3 (A1), U2.3 (A1)
CD1_3V3: J3.9, U1.17 (B1), U2.17 (B1)
CD2: J2.19, U1.4 (A2), U2.4 (A2)
CD2_3V3: J3.10, U1.16 (B2), U2.16 (B2)
CD3: J2.20, U1.5 (A3), U2.5 (A3)
CD3_3V3: J3.11, U1.15 (B3), U2.15 (B3)
CD4: J1.20, U1.6 (A4), U2.6 (A4)
CD4_3V3: J3.12, U1.14 (B4), U2.14 (B4)
CD5: J1.19, U1.7 (A5), U2.7 (A5)
CD5_3V3: J3.13, U1.13 (B5), U2.13 (B5)
CD6: J1.18, U1.8 (A6), U2.8 (A6)
CD6_3V3: J3.14, U1.12 (B6), U2.12 (B6)
CD7: J1.17, U1.9 (A7), U2.9 (A7)
CD7_3V3: J3.15, U1.11 (B7), U2.11 (B7)
CPUCLK: J2.3, U3.13 (B5)
CPUCLK_3V3: J3.5, U3.7 (A5)
G0_3V3: J3.22, J6.5
G1_3V3: J3.21, J6.6
G2_3V3: J3.20, J6.7
G3_3V3: J3.19, J6.8
GND: J1.12, J4.23, J5.5, J5.6, J5.7, J5.8, J6.15, J6.16, U1.1 (DIR), U1.10 (GND), U2.10 (GND), U3.10 (GND), U3.19 (~0E)
GROMCLK: J2.4, U3.12 (B6)
GROMCLK_3V3: J3.6, U3.8 (A6)
HS_3V3: J4.1, J6.13
MODE: J1.13, U3.6 (A4)
MODE_3V3: J3.1, U3.14 (B4)
R0_3V3: J4.11, J6.1
R1_3V3: J4.10, J6.2
R2_3V3: J3.18, J6.3
R3_3V3: J3.17, J6.4
USR1_1V8: J4.2, J5.1
USR2_1V8: J4.3, J5.2
USR3_1V8: J4.4, J5.3
USR4_1V8: J4.5, J5.4
VCC: D1.2 (A), J2.8
VCC_3V3: J4.24, U1.20 (VCC), U2.20 (VCC), U3.20 (VCC)
VDD: D1.1 (K), J4.18, U2.1 (DIR), U3.1 (DIR)
VS_3V3: J3.16, J6.14
~CSR_3V3: J3.3, U3.15 (B3)
~CSR: J1.15, U1.19 (~0E), U3.5 (A3)
~CSW_3V3: J3.2, U3.16 (B2)
~CSW: J1.14, U2.19 (~0E), U3.4 (A2)
~INT_3V3: J3.4, U3.3 (A1)
~INT: J1.16, U3.17 (B1)
~RESET_3V3: J3.7, U3.18 (B0)
~RESET: J2.7, U3.2 (A0)
